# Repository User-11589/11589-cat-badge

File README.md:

no code yet for the actual rps to talk to the displays, will add when created

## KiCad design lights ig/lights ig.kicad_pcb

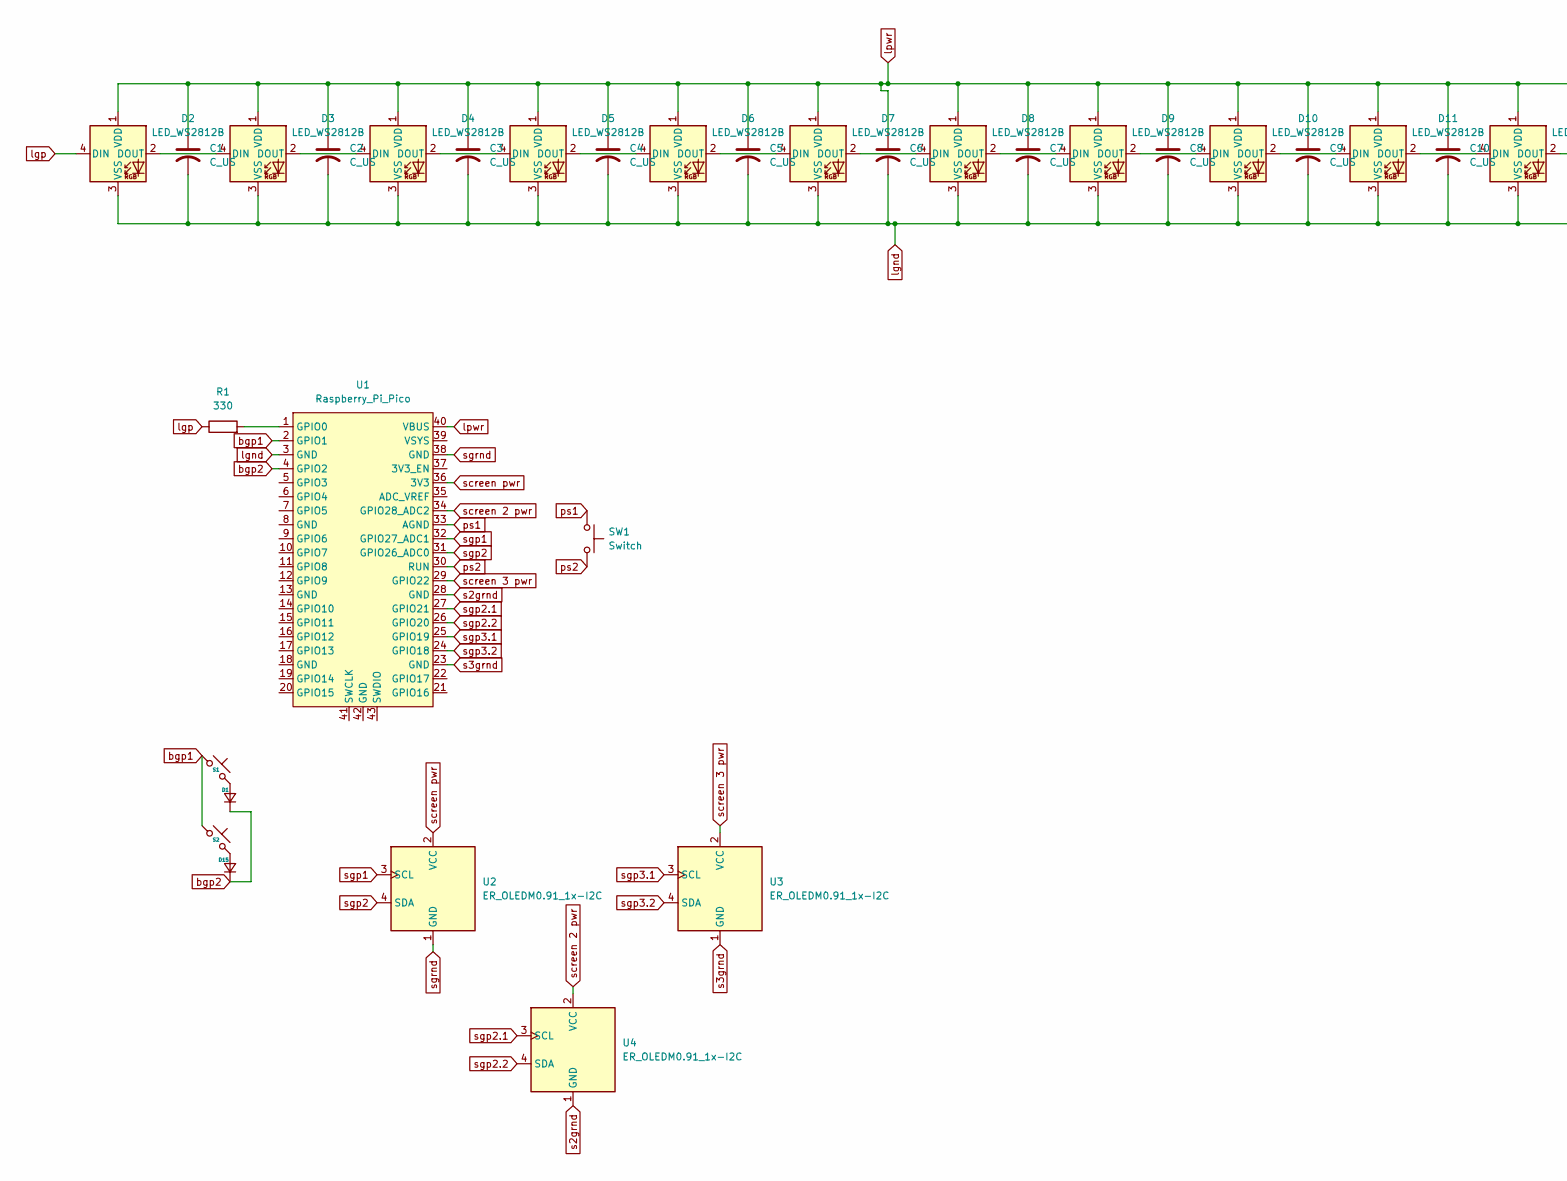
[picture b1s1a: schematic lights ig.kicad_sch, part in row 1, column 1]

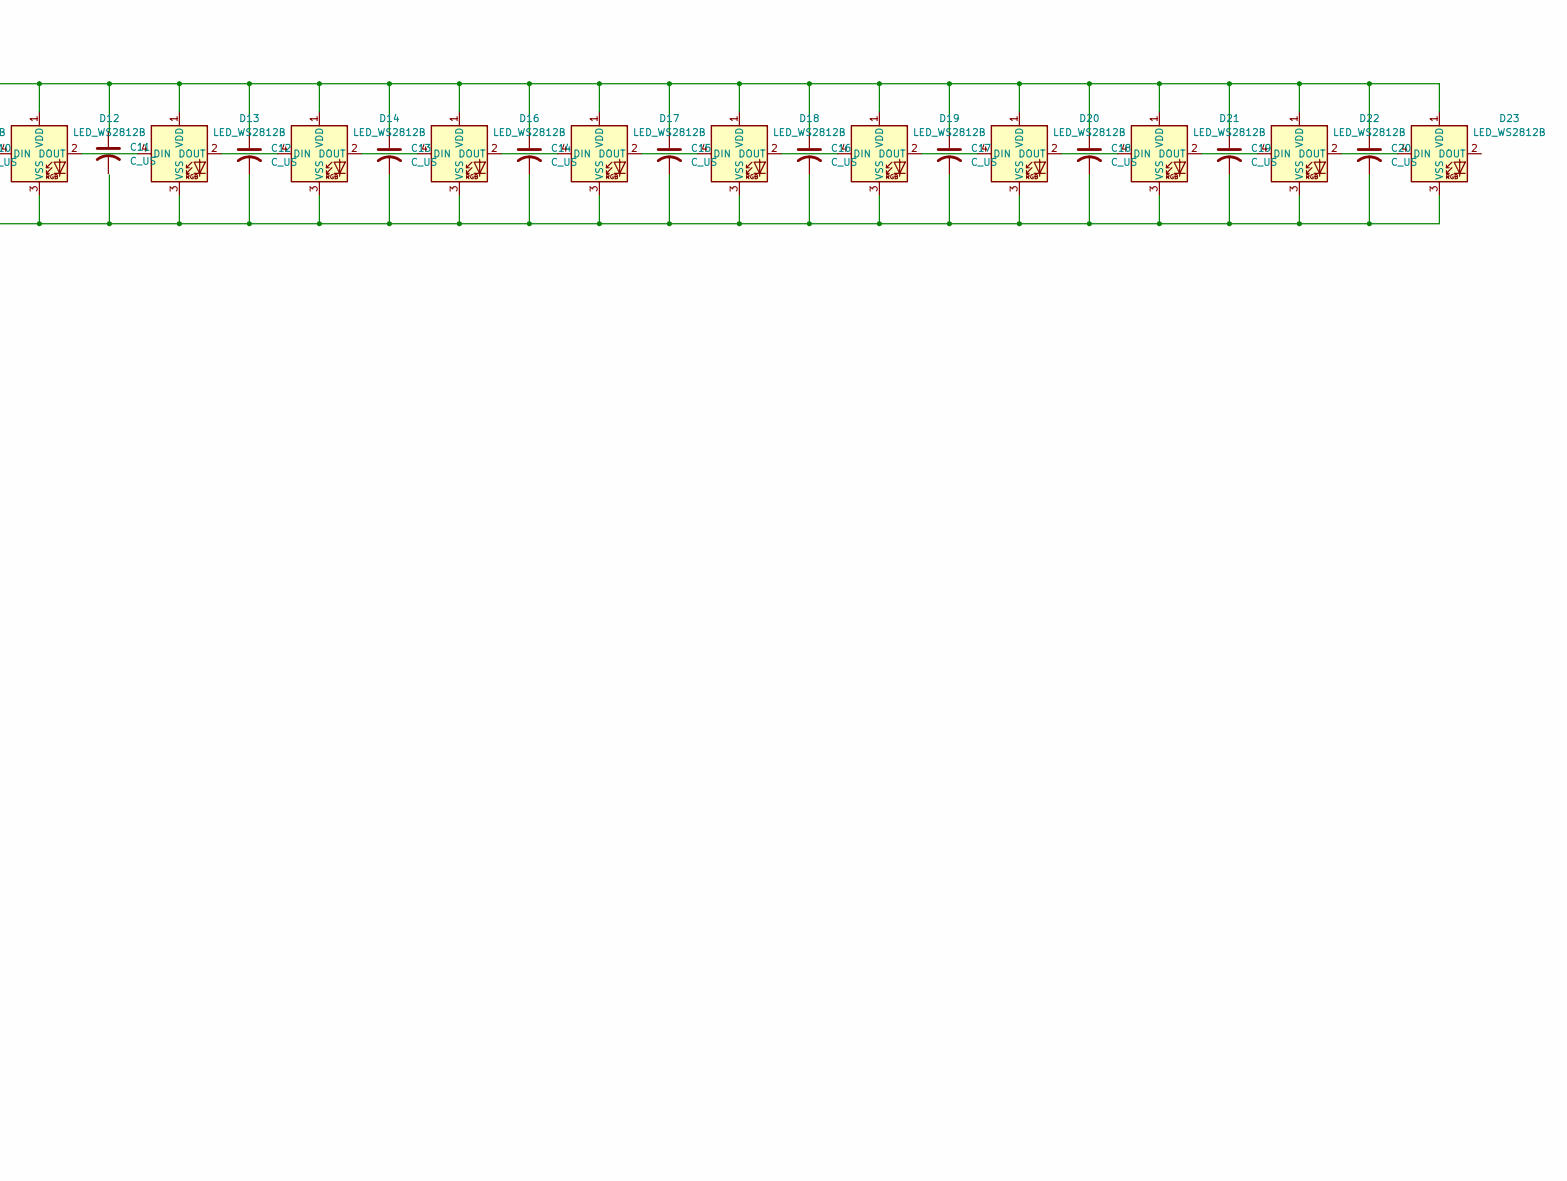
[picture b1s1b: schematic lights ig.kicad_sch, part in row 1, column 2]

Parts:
C1, C2, C3, C4, C5, C6, C7, C8, C9, C10, C11, C12, C13, C14, C15, C16, C17, C18, C19, C20: C_US; WCAP-ATG5_5X11_DXL_
D1, D15: Diode_DO-35
D2, D3, D4, D5, D6, D7, D8, D9, D10, D11, D12, D13, D14, D16, D17, D18, D19, D20, D21, D22, D23: LED_WS2812B
R1: 330; Resistor_0402
S1, S2: SW_Cherry_MX_1.00u_PCB
SW1: Switch; SW_PUSH_6mm
U1: Raspberry_Pi_Pico
U2, U3, U4: ER_OLEDM0.91_1x-I2C

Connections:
unnamed: D1.2 (A), S1.2
unnamed: D2.2 (DOUT), D3.4 (DIN)
unnamed: D3.2 (DOUT), D4.4 (DIN)
unnamed: D4.2 (DOUT), D5.4 (DIN)
unnamed: D5.2 (DOUT), D6.4 (DIN)
unnamed: D6.2 (DOUT), D7.4 (DIN)
unnamed: D7.2 (DOUT), D8.4 (DIN)
unnamed: D8.2 (DOUT), D9.4 (DIN)
unnamed: D9.2 (DOUT), D10.4 (DIN)
unnamed: D10.2 (DOUT), D11.4 (DIN)
unnamed: D11.2 (DOUT), D12.4 (DIN)
unnamed: D12.2 (DOUT), D13.4 (DIN)
unnamed: D13.2 (DOUT), D14.4 (DIN)
unnamed: D14.2 (DOUT), D16.4 (DIN)
unnamed: D15.2 (A), S2.2
unnamed: D16.2 (DOUT), D17.4 (DIN)
unnamed: D17.2 (DOUT), D18.4 (DIN)
unnamed: D18.2 (DOUT), D19.4 (DIN)
unnamed: D19.2 (DOUT), D20.4 (DIN)
unnamed: D20.2 (DOUT), D21.4 (DIN)
unnamed: D21.2 (DOUT), D22.4 (DIN)
unnamed: D22.2 (DOUT), D23.4 (DIN)
unnamed: R1.2, U1.1 (GPIO0)
bgp1: S1.1, S2.1, U1.2 (GPIO1)
bgp2: D1.1 (K), D15.1 (K), U1.4 (GPIO2)
lgnd: C1.2, C2.2, C3.2, C4.2, C5.2, C6.2, C7.2, C8.2, C9.2, C10.2, C12.2, C13.2, C14.2, C15.2, C16.2, C17.2, C18.2, C19.2, C20.2, D2.3 (VSS), D3.3 (VSS), D4.3 (VSS), D5.3 (VSS), D6.3 (VSS), D7.3 (VSS), D8.3 (VSS), D9.3 (VSS), D10.3 (VSS), D11.3 (VSS), D12.3 (VSS), D13.3 (VSS), D14.3 (VSS), D16.3 (VSS), D17.3 (VSS), D18.3 (VSS), D19.3 (VSS), D20.3 (VSS), D21.3 (VSS), D22.3 (VSS), D23.3 (VSS), U1.3 (GND)
lgp: D2.4 (DIN), R1.1
lpwr: C1.1, C2.1, C3.1, C4.1, C5.1, C6.1, C7.1, C8.1, C9.1, C10.1, C12.1, C13.1, C14.1, C15.1, C16.1, C17.1, C18.1, C19.1, C20.1, D2.1 (VDD), D3.1 (VDD), D4.1 (VDD), D5.1 (VDD), D6.1 (VDD), D7.1 (VDD), D8.1 (VDD), D9.1 (VDD), D10.1 (VDD), D11.1 (VDD), D12.1 (VDD), D13.1 (VDD), D14.1 (VDD), D16.1 (VDD), D17.1 (VDD), D18.1 (VDD), D19.1 (VDD), D20.1 (VDD), D21.1 (VDD), D22.1 (VDD), D23.1 (VDD), U1.40 (VBUS)
ps1: SW1.1, U1.33 (AGND)
ps2: SW1.2, U1.30 (RUN)
s2grnd: U1.28 (GND), U4.1 (GND)
s3grnd: U1.23 (GND), U3.1 (GND)
screen 2 pwr: U1.34 (GPIO28_ADC2), U4.2 (VCC)
screen 3 pwr: U1.29 (GPIO22), U3.2 (VCC)
screen pwr: U1.36 (3V3), U2.2 (VCC)
sgp1: U1.32 (GPIO27_ADC1), U2.3 (SCL)
sgp2: U1.31 (GPIO26_ADC0), U2.4 (SDA)
sgp2.1: U1.27 (GPIO21), U4.3 (SCL)
sgp2.2: U1.26 (GPIO20), U4.4 (SDA)
sgp3.1: U1.25 (GPIO19), U3.3 (SCL)
sgp3.2: U1.24 (GPIO18), U3.4 (SDA)
sgrnd: U1.38 (GND), U2.1 (GND)

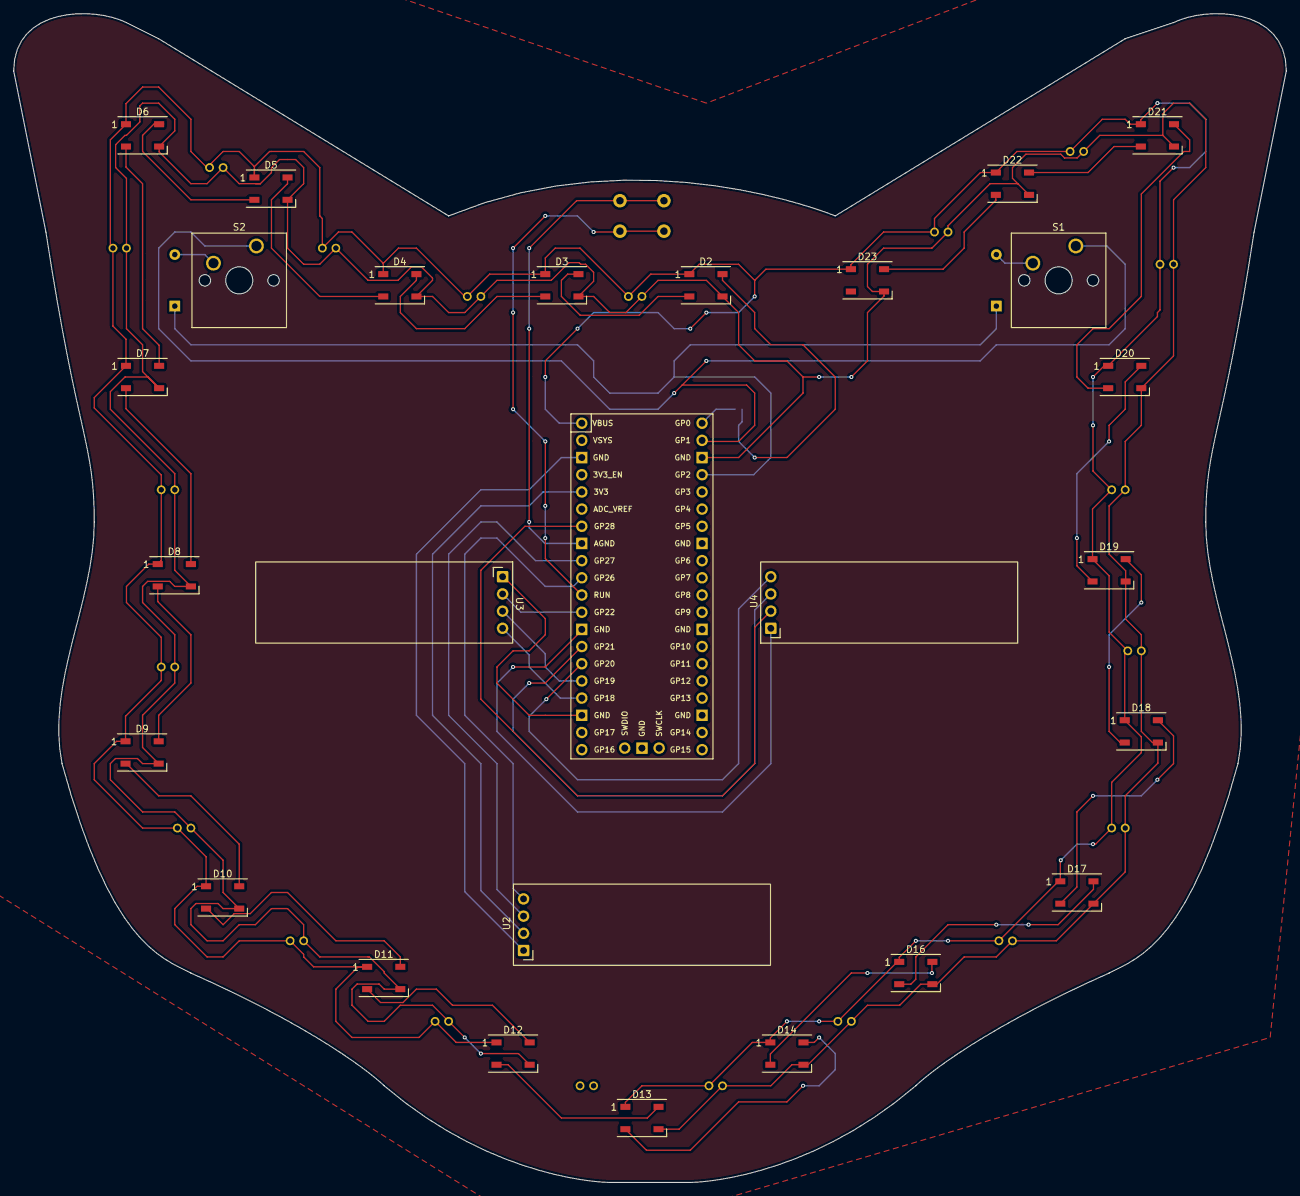
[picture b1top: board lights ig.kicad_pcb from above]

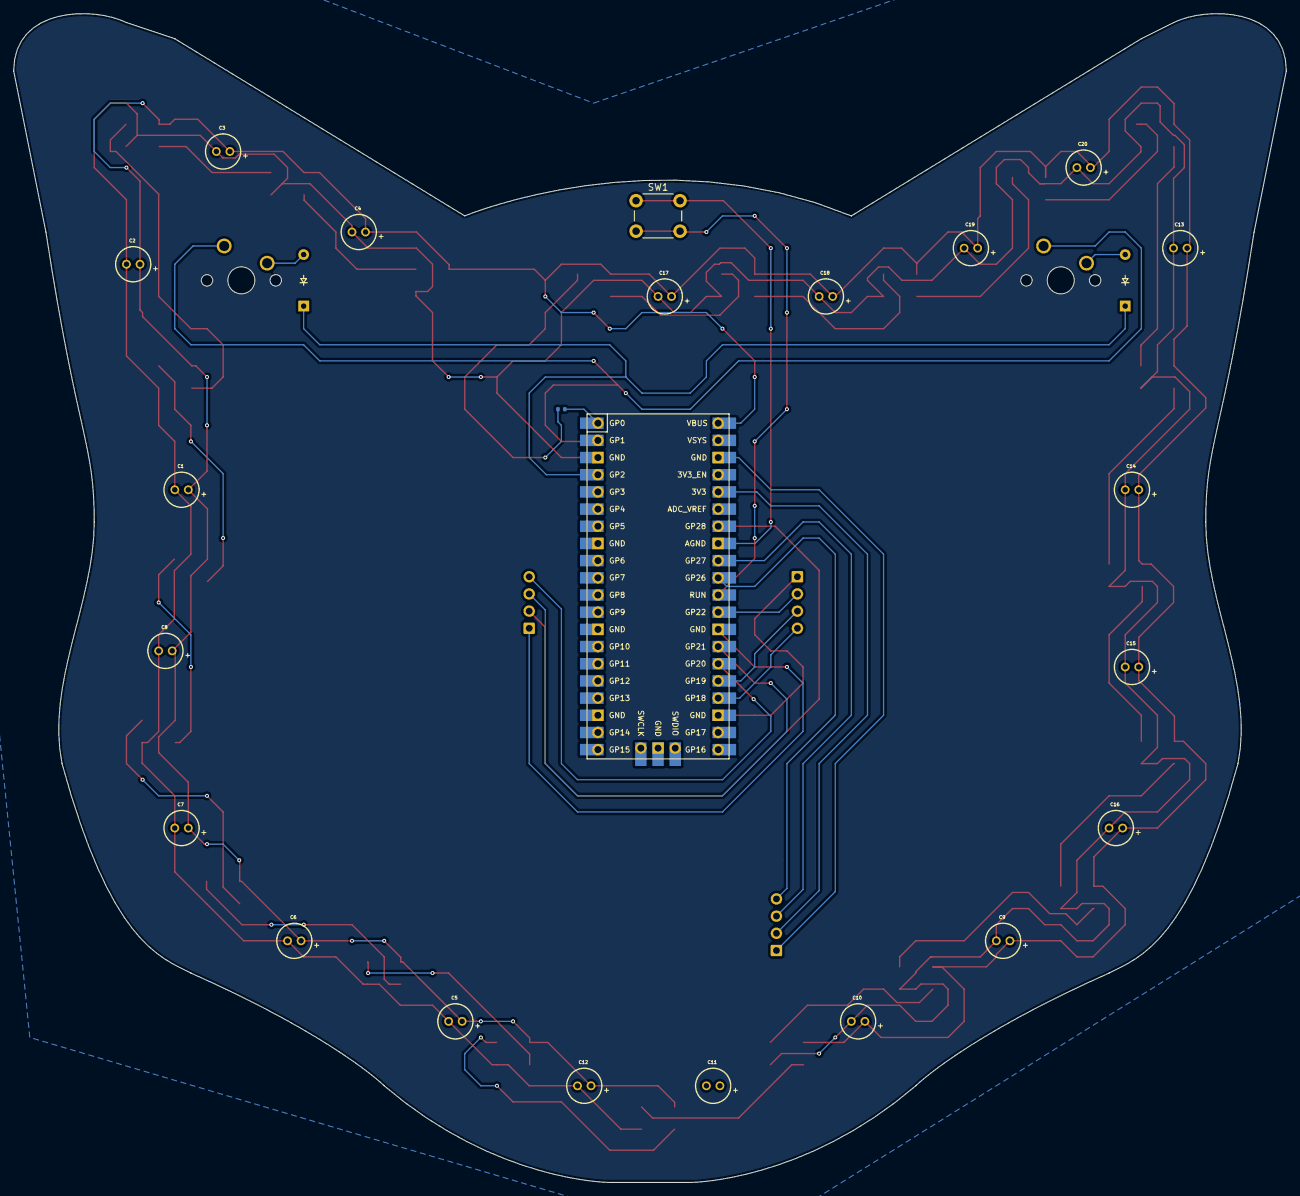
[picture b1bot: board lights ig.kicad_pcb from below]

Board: 2 copper layers, 188.1 x 172.8 mm, 51 parts (25 on the bottom side), 42 nets.

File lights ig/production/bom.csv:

Designator,Footprint,Quantity,Value,LCSC Part #
"C1, C10, C11, C12, C13, C14, C15, C16, C17, C18, C19, C2, C20, C3, C4, C5, C6, C7, C8, C9",WCAP-ATG5_5X11_DXL_,20,C_US,
"D1, D15",Diode_DO-35,2,~,
"D10, D11, D12, D13, D14, D16, D17, D18, D19, D2, D20, D21, D22, D23, D3, D4, D5, D6, D7, D8, D9",LED_WS2812B,21,LED_WS2812B,
R1,Resistor_0402,1,330,
"S1, S2",SW_Cherry_MX_1.00u_PCB,2,~,
SW1,SW_PUSH_6mm,1,Switch,
U1,Raspberry_Pi_Pico,1,Raspberry_Pi_Pico,
"U2, U3, U4",ER_OLEDM0.91_1x-I2C,3,ER_OLEDM0.91_1x-I2C,
